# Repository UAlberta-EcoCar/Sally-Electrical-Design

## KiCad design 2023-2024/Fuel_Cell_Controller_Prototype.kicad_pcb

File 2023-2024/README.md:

# EcoCar Sally Prototype
***This is the official repository for the 2024-2025 EcoCar prototype, Sally***

Much of the systems of this vehicle will build on the innovations implemented in Lucy. Utilizing CANbus, we can easily add more modules to our overall system. We will also be employing power distribution networks alongside CANbus as to create a more intensively modular system.

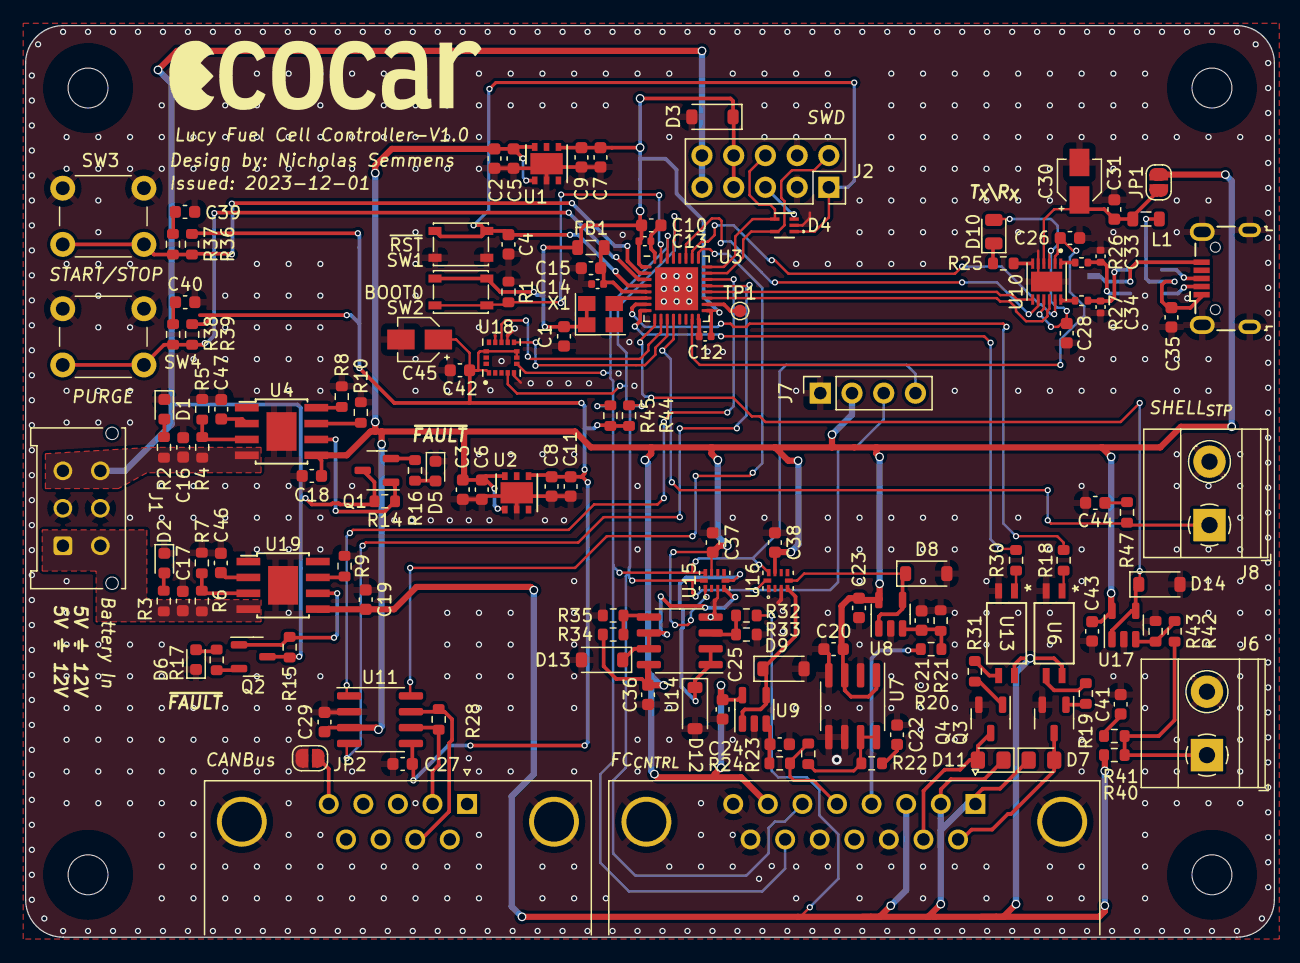
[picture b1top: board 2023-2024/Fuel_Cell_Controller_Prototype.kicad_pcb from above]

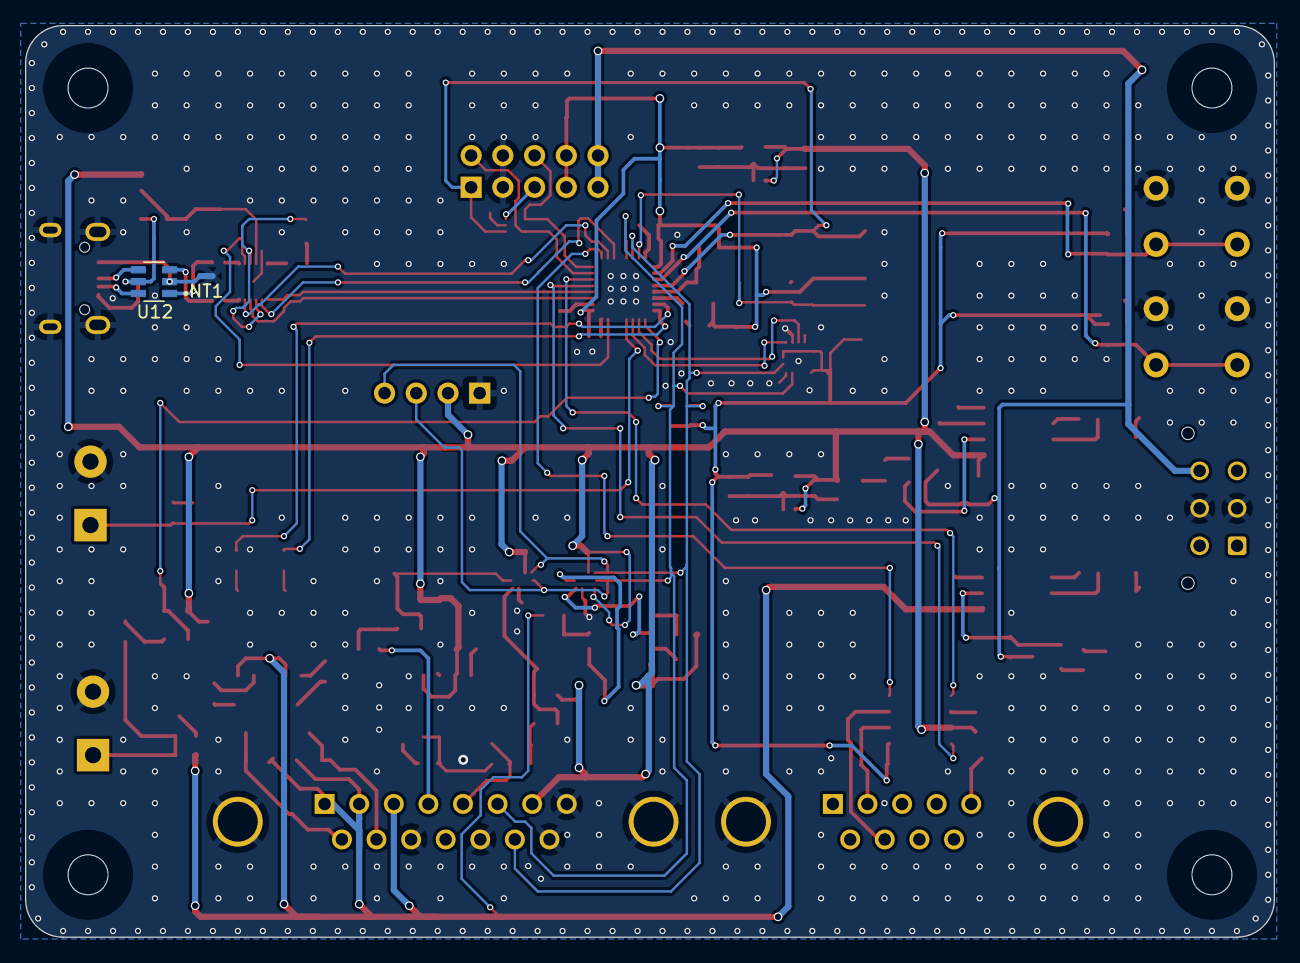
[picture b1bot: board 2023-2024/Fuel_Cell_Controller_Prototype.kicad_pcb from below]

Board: 2 copper layers, 100.0 x 73.0 mm, 148 parts (2 on the bottom side), 89 nets.

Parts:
C1, C4, C5, C6, C9, C11, C23, C25, C26, C27, C28, C29, C31, C35, C36, C37, C38, C42, C43: 100n; C_0603_1608Metric
C2, C3, C7, C8, C15, C16, C17, C18, C19, C24: 1u; C_0603_1608Metric
C10: 4u7; C_0603_1608Metric
C12, C13, C14: 100n; C_0402_1005Metric
C20, C22, C39, C40, C41, C44: 2u2; C_0603_1608Metric
C21: 0u33; C_0603_1608Metric
C30: 4u7; CP_Elec_3x5.3
C33, C34: 47p; C_0402_1005Metric
C45: 10u; CP_Elec_3x5.3
C46, C47: 2n2; C_0603_1608Metric
D1, D2: BLUE; LED_0603_1608Metric
D3, D8, D9, D12, D13, D14: MMSZ5226B-7-F; D_SOD_123_M
D4: ESDALC6V1P5
D5, D6: EMERALD; LED_0603_1608Metric
D7, D11: SD0805S020S1R0; D_0805_2012Metric_Pad1.15x1.40mm_HandSolder
D10: PINK; LED_0805_2012Metric
Display 128x64 0.96" I2C: Display_128x64; Display_128x64_096_I2C
FB1: 600R; L_0805_2012Metric
H1, H2, H3, H4: MountingHole; MountingHole_3.2mm_M3
J1: STD_PWR_HEADER
J2: Conn_02x05_Odd_Even; PinSocket_2x05_P2.54mm_Vertical
J3: DE9_Receptacle; DSUB-9_Female_Horizontal_P2.77x2.84mm_EdgePinOffset7.70mm_H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
J4: DA15_Receptacle_MountingHoles; DSUB-15_Female_Horizontal_P2.77x2.84mm_EdgePinOffset7.70mm_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
J5: USB_B_Micro; USB_Micro-B_Wuerth_629105150521
J6, J8: Screw_Terminal_01x02; TerminalBlock_Phoenix_MKDS-1,5-2-5.08_1x02_P5.08mm_Horizont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
J7: OLED; PinSocket_1x04_P2.54mm_Vertical
JP1, JP2: SolderJumper_2_Open; SolderJumper-2_P1.3mm_Open_RoundedPad1.0x1.5mm
L1: 600R/0.5A; L_0805_2012Metric
NT1: NetTie_2; NetTie-2_SMD_Pad0.5mm
Q1, Q2: SI2302A-TPMSCT-ND; SOT-23-3
Q3, Q4: FMMT491ATA; SOT-23-3
R1, R5, R7, R24, R36, R37, R38, R39, R40, R41, R47: 10k; R_0603_1608Metric
R2, R16, R17: 270; R_0603_1608Metric
R3, R43: 820; R_0603_1608Metric
R4: 11k; R_0603_1608Metric
R6: 900; R_0603_1608Metric
R8: 400k; R_0603_1608Metric
R9, R10: 1k; R_0603_1608Metric
R14, R15, R23: 100k; R_0603_1608Metric
R18, R30: 422; R_0603_1608Metric
R19, R31: 249; R_0603_1608Metric
R20: 6.8k; R_0603_1608Metric
R21, R33, R34, R35: 13k; R_0603_1608Metric
R22, R25: 51; R_0603_1608Metric
R26, R27: 33; R_0402_1005Metric
R28: 120; R_0603_1608Metric
R32: 51k; R_0603_1608Metric
R42: 2.2k; R_0603_1608Metric
R44, R45: 4.7k; R_0603_1608Metric
SW1, SW2: PTS815 SJM 250 SMTR LFS; SW_SPST_PTS810
SW3, SW4: SW_PUSH_6mm_H5mm
TP1: MCO; TestPoint_Pad_D1.0mm
U1, U2: LD39050PU33R; DFN-6-1EP_3x3mm_P0.95mm_EP1.7x2.6mm
U3: STM32L432KCUx; QFN-32-1EP_5x5mm_P0.5mm_EP3.45x3.45mm
U4, U19: TPS259621; TI_SO-PowerPAD-8
U6, U13: EL3H7(B)(TA)-VG; SOIC_BTA-VG_EVS
U7: MCP1501-33E/SN; SOIC-8_3.9x4.9mm_P1.27mm
U8, U9, U17: AD8603; TSOT-23-5
U10: FT234XD-R; SON45P300X300X80-13N
U11: MCP2542FD-E/SN; SOIC-8_3.9x4.9mm_P1.27mm
U12: USBLC6-2SC6
U14: MCP602-E/SN; SOIC-8_3.9x4.9mm_P1.27mm
U15, U16: ADS1115IRUGR; IC_ADS1115IRUGR
U18: LIS3DHTR; XDCR_LIS3DHTR
X1: OXETDLJANF-8MHZ; Crystal_SMD_3225-4Pin_3.2x2.5mm

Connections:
+3V3: C8.2, C11.2, C27.1, C42.2, C45.1, R37.2, R38.2, R44.2, R45.2, U2.4 (VO), U11.5 (VIO), U18.1 (VDD_IO), U18.7 (SDO/SA0), U18.8 (CS), U18.14 (VDD)
+5V: C2.2, C3.2, C5.2, C6.2, C18.2, C20.1, C23.2, C25.2, C29.2, C36.2, C37.2, C38.2, C43.2, J4.7, J7.2, JP1.2 (B), R34.1, U1.1 (EN), U1.6 (VI), U2.1 (EN), U2.6 (VI), U4.5 (OUT), U7.1 (VDD), U7.3 (~SHDN), U8.5 (V+), U9.5 (V+), U11.3 (VDD), U14.8 (V+), U15.1 (ADDR), U15.8 (VDD), U16.8 (VDD), U17.5 (V+)
+12V: C19.2, D7.1 (K), D11.1 (K), J4.1, J4.2, J4.3, R32.1, R40.1, U6.4, U13.4, U19.5 (OUT)
/BOOT0: R1.2, SW2.1, U3.31 (PH3)
/BTN_{1}: R36.2, R37.1, SW3.2, U3.2 (PC14)
/BTN_{2}: R38.1, R39.2, SW4.2, U3.3 (PC15)
/FLT_{5}: Q1.1 (G), R14.1, U4.6 (~FAULT)
/FLT_{12}: Q2.1 (G), R15.1, U19.6 (~FAULT)
/IO /BTN_{RTN}: J6.1, R40.2, R41.1, R42.2
/IO /CAN_H: J3.7, R28.2, U11.7 (CANH)
/IO /CAN_L: J3.2, R28.1, U11.6 (CANL)
/IO /D+: J5.3 (D+), U12.4
/IO /D-: J5.2 (D-), U12.6
/IO /DM: C33.1, R26.2, U12.1
/IO /DP: C34.1, R27.2, U12.3
/IO /FC_{TEMP}: D9.1, U9.1, U9.4 (-), U16.4 (AIN0)
/IO /GND_{1}: J5.5 (GND), NT1.2, U12.2
/IO /H2_{PRS}: D8.1, U8.1, U8.4 (-), U16.5 (AIN1)
/IO /PA0: U3.6 (PA0), X1.3 (OUT)
/IO /PA1: R18.2, U3.7 (PA1)
/IO /PA2: R30.2, U3.8 (PA2)
/IO /PA3: D14.1, U3.9 (PA3), U17.1, U17.4 (-)
/IO /PA4: U3.10 (PA4), U18.11 (INT1)
/IO /PA5: U3.11 (PA5), U18.9 (INT2)
/IO /PA6: J8.1, R47.1, U3.12 (PA6)
/IO /PA8: TP1.1, U3.18 (PA8)
/IO /PA9: U3.19 (PA9), U10.10 (RXD)
/IO /PA10: U3.20 (PA10), U10.7 (TXD)
/IO /PA11: U3.21 (PA11), U11.4 (RXD)
/IO /PA12: U3.22 (PA12), U11.1 (TXD)
/IO /PA13: D4.5, J2.2, U3.23 (PA13)
/IO /PA14: D4.4, J2.6, U3.24 (PA14)
/IO /PA15: U3.25 (PA15), U11.8 (STBY)
/IO /PB1: C26.2, U3.15 (PB1), U10.2 (~RESET#)
/IO /PB3: U3.26 (PB3), U10.11 (CTS#)
/IO /PB4: U3.27 (PB4), U10.8 (RTS#)
/IO /PB6: J4.6, J7.3, R44.1, U3.29 (PB6), U15.10 (SCL), U16.10 (SCL), U18.4 (SCL/SPC)
/IO /PB7: J4.14, J7.4, R45.1, U3.30 (PB7), U15.9 (SDA), U16.9 (SDA), U18.6 (SDA/SDI/SDO)
/IO /PRESSURE_SIG: J4.4, R20.2
/IO /PURGE_RTN: D11.2 (A), J4.10, Q4.3 (C)
/IO /Purge_Valve_Switch/V_{E}: R31.1, U13.3
/IO /SHIELD: J3.5, JP2.2 (B)
/IO /SUPPLY_RTN: D7.2 (A), J4.9, Q3.3 (C)
/IO /Supply_Valve_Switch/V_{E}: R19.1, U6.3
/IO /THERM_{VREF}: J4.5, R23.2, R24.2
/IO /VCCIO: C28.1, D10.2 (A), U10.3 (3V3OUT), U10.9 (VCCIO)
/IO /V_{BUS}: C35.1, J5.1 (VBUS), L1.2, U12.5
/MCU_3V3: C1.1, C7.2, C9.2, C10.1, C12.1, C13.1, D3.1, FB1.1, J2.7, J2.8, SW2.2, U1.4 (VO), U3.1 (VDD), U3.17 (VDD), X1.1 (Tri-State), X1.4 (VDD)
/On-Board Sensors/5V_{REF}: D13.1, U14.6 (-), U14.7, U15.4 (AIN0)
/On-Board Sensors/12V_{REF}: D12.1, U14.1, U14.2 (-), U15.5 (AIN1)
/SW_{IM}: D4.3, J2.5
/~RST: C4.1, D4.1, J2.1, SW1.2, U3.4 (NRST)
GNDA: C1.2, C2.1, C3.1, C4.2, C5.1, C6.1, C7.1, C8.1, C9.1, C10.2, C11.1, C12.2, C13.2, C14.2, C15.2, C16.1, C17.1, C18.1, C19.1, C20.2, C21.2, C22.2, C23.1, C24.2, C25.1, C26.1, C27.2, C28.2, C29.1, C30.2, C31.2, C33.2, C34.2, C35.2, C36.1, C37.1, C38.1, C39.2, C40.2, C41.2, C42.1, C43.1, C44.2, C45.2, C46.1, C47.1, D1.1 (K), D2.1 (K), D3.2, D4.2, D5.1 (K), D6.1 (K), D8.2, D9.2, D12.2, D13.2, D14.2, J1.2 (GND), J1.5 (GND), J2.3, J2.4, J3.0 (PAD), J4.0 (PAD), J4.8, J4.11 (P111), J4.13, J4.15, J5.6 (Shield), J6.2, J7.1, J8.2, JP2.1 (A), NT1.1, Q3.2 (E), Q4.2 (E), R1.1, R5.1, R7.1, R8.1, R9.1, R10.1, R21.2, R33.2, R35.2, R43.2, SW1.1, SW3.1, SW4.1, U1.2 (GND), U1.7 (GND), U2.2 (GND), U2.7 (GND), U3.16 (VSS), U3.32 (VSS), U3.33 (VSS), U4.1 (GND), U4.9 (PAD), U6.2, U7.2 (GND), U7.4 (GND), U7.5 (GND), U7.6 (GND), U8.2 (V-), U9.2 (V-), U10.5 (GND), U10.13 (GND__1), U11.2 (VSS), U13.2, U14.4 (V-), U15.3 (GND), U16.1 (ADDR), U16.3 (GND), U17.2 (V-), U18.5 (GND), U18.10 (RES), U18.12 (GND__1), U19.1 (GND), U19.9 (PAD), X1.2 (GND)
unnamed: C22.1, R22.2
unnamed: C39.1, R36.1
unnamed: C40.1, R39.1
unnamed: C41.1, R41.2
unnamed: C44.1, R47.2
unnamed: D1.2 (A), R2.1
unnamed: D2.2 (A), R3.1
unnamed: D5.2 (A), R16.1
unnamed: D6.2 (A), R17.1
unnamed: D10.1 (K), R25.1
unnamed: C30.1, C31.1, JP1.1 (A), L1.1, U10.4 (VCC)
unnamed: Q1.2 (S), R16.2
unnamed: Q2.2 (S), R17.2
unnamed: Q3.1 (B), R19.2
unnamed: Q4.1 (B), R31.2
unnamed: R18.1, U6.1
unnamed: R30.1, U13.1
unnamed: C14.1, C15.1, FB1.2, U3.5 (VDDA)
unnamed: R4.1, R5.2, U4.3 (EN/UVLO)
unnamed: R10.2, U4.7 (ILM)
unnamed: R8.2, U4.8 (OVLO)
unnamed: C47.2, U4.2 (dV/dT)
unnamed: R22.1, R23.1, U7.7 (OUT), U7.8 (FB)
unnamed: C21.1, R20.1, R21.1, U8.3 (+)
unnamed: C24.1, R24.1, U9.3 (+)
unnamed: R25.2, U10.6 (CBUS0)
unnamed: R26.1, U10.1 (USBDM)
unnamed: R27.1, U10.12 (USBDP)
unnamed: R32.2, R33.1, U14.3 (+)
unnamed: R34.2, R35.1, U14.5 (+)
unnamed: R42.1, R43.1, U17.3 (+)
unnamed: R6.1, R7.2, U19.3 (EN/UVLO)
unnamed: R9.2, U19.7 (ILM)
unnamed: C46.2, U19.2 (dV/dT)
UNPROTECTED_5V: C16.2, J1.3 (5V), J1.6 (5V), J2.9, J2.10, Q1.3 (D), Q2.3 (D), R2.2, R4.2, R14.2, R15.2, U4.4 (IN)
UNPROTECTED_12V: C17.2, J1.1 (12V), J1.4 (12V), R3.2, R6.2, U19.4 (IN)

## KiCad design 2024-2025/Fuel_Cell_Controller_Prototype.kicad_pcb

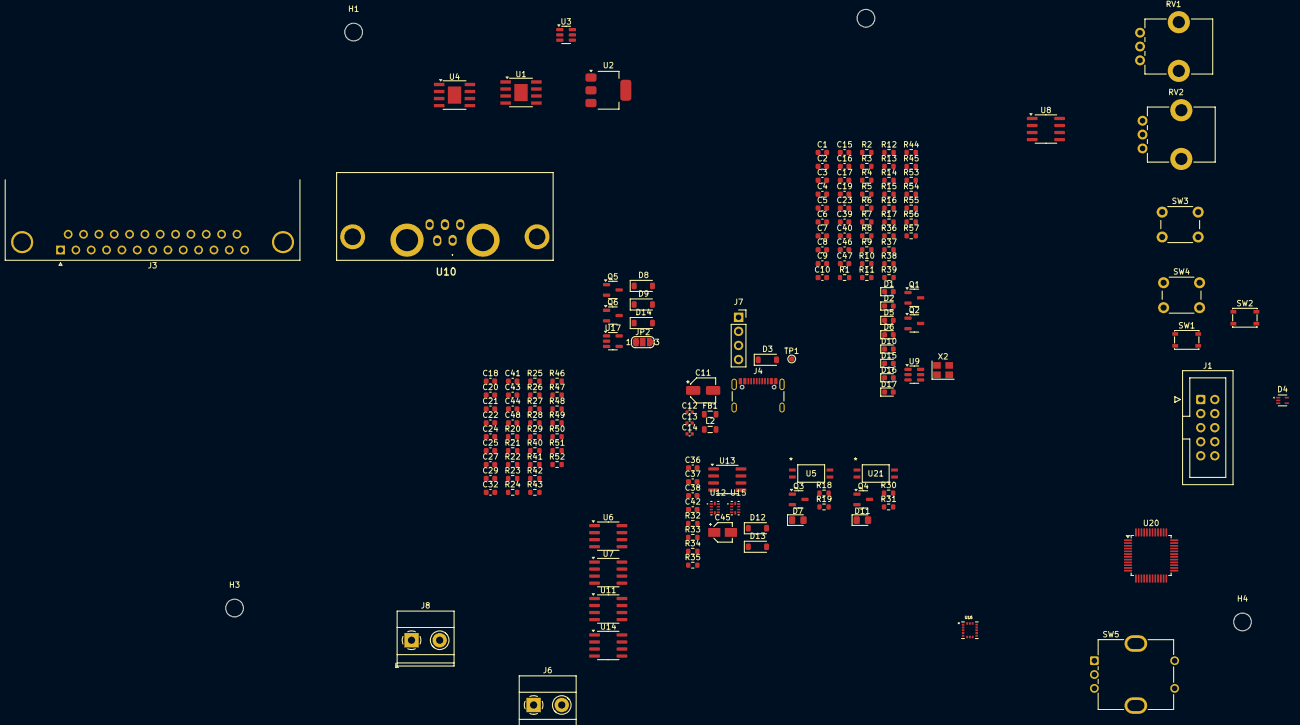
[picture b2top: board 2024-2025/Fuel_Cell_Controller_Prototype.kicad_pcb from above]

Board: 2 copper layers, 163 parts (0 on the bottom side), 108 nets, no tracks yet.

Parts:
C1, C4, C5, C8, C23, C25, C27, C29, C36, C37, C38, C42, C43, C48: 100n; C_0603_1608Metric
C2, C3, C6: 10u; C_0603_1608Metric
C7: 22u; C_0603_1608Metric
C9: 47u; C_0603_1608Metric
C10: 4u7; C_0603_1608Metric
C11: 47u; CP_Elec_4x5.4
C12, C13, C14: 100n; C_0402_1005Metric
C15, C16, C17, C19, C24: 1u; C_0603_1608Metric
C18, C32: 10n; C_0603_1608Metric
C20, C22, C39, C40, C41, C44: 2u2; C_0603_1608Metric
C21: 0u33; C_0603_1608Metric
C45: 10u; CP_Elec_3x5.3
C46, C47: 2n2; C_0603_1608Metric
D1, D2: BLUE; LED_0603_1608Metric
D3, D8, D9, D12, D13, D14: MMSZ5226B-7-F; D_SOD_123_M
D4: ESDALC6V1P5
D5, D6: EMERALD; LED_0603_1608Metric
D7, D11: SD0805S020S1R0; D_0805_2012Metric_Pad1.15x1.40mm_HandSolder
D10, D15, D16, D17: RED; LED_0603_1608Metric
Display 128x64 0.96" I2C: Display_128x64; Display_128x64_096_I2C
FB1: 600R; L_0805_2012Metric
H1, H2, H3, H4: MountingHole; MountingHole_3.2mm_M3
J1: STM32-Prog-Header; IDC-STM32-Prog-Header_2x05_P2.54mm_Vertical
J3: DB25_Receptacle_MountingHoles; DSUB-25_Female_Horizontal_P2.77x2.84mm_EdgePinOffset9.90mm_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
J4: USB_C_Receptacle_USB2.0_14P; USB_C_Receptacle_GCT_USB4105-xx-A_16P_TopMnt_Horizontal
J6, J8: Screw_Terminal_01x02; TerminalBlock_Phoenix_MKDS-1,5-2-5.08_1x02_P5.08mm_Horizont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
J7: OLED; PinSocket_1x04_P2.54mm_Vertical
JP2: SolderJumper_3_Open; SolderJumper-3_P1.3mm_Open_RoundedPad1.0x1.5mm_NumberLabels
L2: 3.3u; L_0805_2012Metric
Q1, Q2, Q5, Q6: SI2302A-TPMSCT-ND; SOT-23-3
Q3, Q4: FMMT491ATA; SOT-23-3
R1, R7, R11, R12, R24, R25, R26, R27, R29, R36, R37, R38, R39, R40, R41, R46, R47, R48, R49, R50, R51, R52: 10k; R_0603_1608Metric
R2, R16, R17: 270; R_0603_1608Metric
R3, R43: 820; R_0603_1608Metric
R4: 8k; R_0603_1608Metric
R5, R6, R9, R10, R57: 1k; R_0603_1608Metric
R8: 1.2k; R_0603_1608Metric
R13: 54.9k; R_0603_1608Metric
R14, R15, R23: 100k; R_0603_1608Metric
R18, R30: 422; R_0603_1608Metric
R19, R31: 249; R_0603_1608Metric
R20: 6.8k; R_0603_1608Metric
R21, R33, R34, R35: 13k; R_0603_1608Metric
R22: 51; R_0603_1608Metric
R28: 120; R_0603_1608Metric
R32: 51k; R_0603_1608Metric
R42: 2.2k; R_0603_1608Metric
R44, R45: 4.7k; R_0603_1608Metric
R53, R54, R55, R56: 220; R_0603_1608Metric
RV1: Purge_Delay; Potentiometer_Bourns_PTV09A-1_Single_Vertical
RV2: Purge_Duration; Potentiometer_Bourns_PTV09A-1_Single_Vertical
SW1, SW2: PTS815 SJM 250 SMTR LFS; SW_SPST_PTS810
SW3, SW4: SW_PUSH_6mm_H5mm
SW5: RotaryEncoder_Switch; RotaryEncoder_Bourns_Vertical_PEC12R-3x17F-Sxxxx
TP1: MCO; TestPoint_Pad_D1.0mm
U1, U4: TPS259631; TI_SO-PowerPAD-8
U2: AZ1117IH-3.3; SOT-223-3_TabPin2
U3: TPS565208; SOT-23-6
U5, U21: EL3H7(B)(TA)-VG; SOIC_BTA-VG_EVS
U6, U8, U13, U14: MCP6007; SOIC-8_3.9x4.9mm_P1.27mm
U7: MCP1501-33E/SN; SOIC-8_3.9x4.9mm_P1.27mm
U9: USBLC6-2SC6; SOT-23-6
U10: CANConnector; DB7W2-Male
U11: MCP2542FD-E/SN; SOIC-8_3.9x4.9mm_P1.27mm
U12, U15: ADS1115IRUGR; IC_ADS1115IRUGR
U16: LIS3DHTR; XDCR_LIS3DHTR
U17: AD8603; TSOT-23-5
U20: STM32G491CETx; LQFP-48_7x7mm_P0.5mm
X2: OXETDLJANF-8MHZ; Crystal_SMD_3225-4Pin_3.2x2.5mm

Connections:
+3.3V: C1.1, RV1.3, RV2.3, X2.1 (Tri-State), X2.4 (VDD)
+3V3: C7.2, C10.1, C12.1, C13.1, C14.1, C15.1, C27.1, C42.2, C45.1, D3.1, FB1.1, FB1.2, JP2.3 (B), R25.2, R26.2, R29.1, R37.2, R38.2, R44.2, R45.2, R46.1, R50.2, R51.2, SW2.2, U2.2 (VO), U11.5 (VIO), U16.1 (VDD_IO), U16.7 (SDO/SA0), U16.8 (CS), U16.14 (VDD), U20.1 (VBAT), U20.20 (VREF+), U20.21 (VDDA), U20.24 (VDD), U20.36 (VDD), U20.48 (VDD)
+5V: C9.1, C11.1, C20.1, C23.1, C25.1, C29.2, C36.2, C37.2, C38.2, C48.1, J3.12, J7.2, L2.2, R13.1, R34.1, U6.8 (V+), U7.1 (VDD), U7.3 (~SHDN), U8.8 (V+), U11.3 (VDD), U12.1 (ADDR), U12.8 (VDD), U13.8 (V+), U14.8 (V+), U15.8 (VDD)
+7V: C6.2, U1.5 (OUT), U2.3 (VI)
+12V: C2.1, C3.1, C5.1, C19.2, D7.1 (K), D11.1 (K), J3.1, J3.2, J3.3, J3.10, J3.11, J3.23, J3.24, JP2.1 (A), R11.2, R32.1, R40.1, U3.3 (VIN), U4.5 (OUT), U5.4, U21.4
/BTN_{1}: R36.2, R37.1, SW3.2, U20.3 (PC14)
/BTN_{2}: R38.1, R39.2, SW4.2, U20.4 (PC15)
/FLT_{7}: Q1.1 (G), R14.1, U1.6 (~FAULT)
/FLT_{12}: Q2.1 (G), R15.1, U4.6 (~FAULT)
/IO /BTN_{RTN}: J6.1, R40.2, R41.1, R42.2
/IO /CAN_H: R28.2, U10.1, U11.7 (CANH)
/IO /CAN_L: R28.1, U10.3, U11.6 (CANL)
/IO /FC_{TEMP}: D9.1, U14.6 (-), U14.7, U15.4 (AIN0)
/IO /H2_{PRS}: D8.1, U14.1, U14.2 (-), U15.5 (AIN1)
/IO /PA0: J8.1, R47.1, U20.8 (PA0)
/IO /PA1: D14.1, U17.1, U17.4 (-), U20.9 (PA1)
/IO /PA2: R52.1, U20.10 (PA2)
/IO /PA3: R27.1, U20.11 (PA3)
/IO /PA4: SW5.S1, U20.12 (PA4)
/IO /PA5: U16.11 (INT1), U20.13 (PA5)
/IO /PA6: U16.9 (INT2), U20.14 (PA6)
/IO /PA7: J3.8, R51.1, U20.15 (PA7)
/IO /PA8: TP1.1, U20.30 (PA8)
/IO /PA9: J3.21, R50.1, U20.31 (PA9)
/IO /PA10: J3.9, R25.1, U20.32 (PA10)
/IO /PA11: U9.6 (I/O1), U20.33 (PA11)
/IO /PA12: U9.4 (I/O2), U20.34 (PA12)
/IO /PA13: D4.5, J1.4 (SWDIO), U20.37 (PA13)
/IO /PA14: D4.4, J1.2 (SWCLK), U20.38 (PA14)
/IO /PB0: R30.2, U20.16 (PB0)
/IO /PB1: R18.2, U20.17 (PB1)
/IO /PB2: R54.2, U20.18 (PB2)
/IO /PB3: U6.3 (+), U20.40 (PB3)
/IO /PB4: U6.5 (+), U20.41 (PB4)
/IO /PB5: U11.4 (RXD), U20.42 (PB5)
/IO /PB6: R53.2, U20.43 (PB6)
/IO /PB7: J3.19, J7.4, R45.1, U12.9 (SDA), U15.9 (SDA), U16.6 (SDA/SDI/SDO), U20.44 (PB7)
/IO /PB8: J3.6, J7.3, R1.2, R44.1, SW2.1, U12.10 (SCL), U15.10 (SCL), U16.4 (SCL/SPC), U20.39 (PA15), U20.45 (PB8)
/IO /PB9: R55.2, U20.46 (PB9)
/IO /PB10: R56.2, U20.22 (PB10)
/IO /PB11: U11.8 (STBY), U20.25 (PB11)
/IO /PB12: J3.22, R26.1, U20.26 (PB12)
/IO /PB13: U11.1 (TXD), U20.27 (PB13)
/IO /PB14: U8.6 (-), U8.7, U20.28 (PB14)
/IO /PB15: U8.1, U8.2 (-), U20.29 (PB15)
/IO /PRESSURE_SIG: J3.4, R20.2
/IO /PURGE_RTN: D11.2 (A), J3.15, Q4.3 (C)
/IO /PWM_{1,Buff}: J3.7, Q6.3 (D), R49.1
/IO /PWM_{2,Buff}: J3.20, Q5.3 (D), R48.1
/IO /Purge_Valve_Switch/V_{E}: R31.1, U21.3
/IO /SUPPLY_RTN: D7.2 (A), J3.14, Q3.3 (C)
/IO /Supply_Valve_Switch/V_{E}: R19.1, U5.3
/IO /THERM_{VREF}: J3.5, R23.2, R24.2
/On-Board Sensors/5V_{REF}: D13.1, U12.4 (AIN0), U13.6 (-), U13.7
/On-Board Sensors/12V_{REF}: D12.1, U12.5 (AIN1), U13.1, U13.2 (-)
/PF0: U20.5 (PF0), X2.3 (OUT)
/P_Delay: RV1.2, U8.3 (+)
/P_Dur: RV2.2, U8.5 (+)
/VBUS: J4.A4 (VBUS), J4.A9 (VBUS), J4.B4 (VBUS), J4.B9 (VBUS), U9.5 (VBUS)
/~RST: C4.1, SW1.2, U20.7 (PG10)
GNDA: C1.2, C2.2, C3.2, C4.2, C5.2, C6.1, C7.1, C9.2, C10.2, C11.2, C12.2, C13.2, C14.2, C15.2, C16.1, C17.1, C18.2, C19.1, C20.2, C21.2, C22.2, C23.2, C24.2, C25.2, C27.2, C29.1, C32.2, C36.1, C37.1, C38.1, C39.2, C40.2, C41.2, C42.1, C43.1, C44.2, C45.2, C46.1, C47.1, C48.2, D1.1 (K), D2.1 (K), D3.2, D4.2, D8.2, D9.2, D10.1 (K), D12.2, D13.2, D14.2, D15.1 (K), D16.1 (K), D17.1 (K), J1.5 (GND), J1.6 (GND), J3.0 (PAD), J3.13, J3.16, J3.18, J3.25, J4.A1 (GND), J4.A12 (GND), J4.B1 (GND), J4.B12 (GND), J4.S1 (SHIELD), J6.2, J7.1, J8.2, Q1.2 (S), Q2.2 (S), Q3.2 (E), Q4.2 (E), Q5.2 (S), Q6.2 (S), R1.1, R8.1, R9.1, R10.1, R12.1, R21.2, R33.2, R35.2, R43.2, R57.1, RV1.1, RV2.1, SW1.1, SW3.1, SW4.1, SW5.C, SW5.S2, U1.1 (GND), U1.9 (PAD), U2.1 (GND), U3.1 (GND), U4.1 (GND), U4.9 (PAD), U5.2, U6.4 (V-), U7.2 (GND), U7.4 (GND), U7.5 (GND), U7.6 (GND), U8.4 (V-), U9.2 (GND), U10.8 (A1), U11.2 (VSS), U12.3 (GND), U13.4 (V-), U14.4 (V-), U15.1 (ADDR), U15.3 (GND), U16.5 (GND), U16.10 (RES), U16.12 (GND__1), U17.2 (V-), U20.19 (VSSA), U20.23 (VSS), U20.35 (VSS), U20.47 (VSS), U21.2, X2.2 (GND)
unnamed: C18.1, R29.2, R52.2, SW5.A
unnamed: C22.1, R22.2
unnamed: C32.1, R27.2, R46.2, SW5.B
unnamed: C39.1, R36.1
unnamed: C40.1, R39.1
unnamed: C41.1, R41.2
unnamed: C44.1, R47.2
unnamed: D1.2 (A), R2.1
unnamed: D2.2 (A), R3.1
unnamed: D5.2 (A), R16.1
unnamed: D5.1 (K), Q1.3 (D)
unnamed: D6.2 (A), R17.1
unnamed: D6.1 (K), Q2.3 (D)
unnamed: D10.2 (A), R53.1
unnamed: D15.2 (A), R54.1
unnamed: D16.2 (A), R55.1
unnamed: D17.2 (A), R56.1
unnamed: J4.A6 (D+), J4.B6 (D+), U9.3 (I/O2)
unnamed: J4.A7 (D-), J4.B7 (D-), U9.1 (I/O1)
unnamed: JP2.2 (C), R48.2, R49.2
unnamed: Q3.1 (B), R19.2
unnamed: Q4.1 (B), R31.2
unnamed: Q5.1 (G), U6.6 (-), U6.7
unnamed: Q6.1 (G), U6.1, U6.2 (-)
unnamed: R18.1, U5.1
unnamed: R30.1, U21.1
unnamed: R4.1, R5.2, U1.3 (EN/UVLO)
unnamed: R10.2, U1.7 (ILM)
unnamed: R5.1, R8.2, U1.8 (OVLO)
unnamed: C47.2, U1.2 (dV/dT)
unnamed: R11.1, U3.5 (EN)
unnamed: C8.1, L2.1, U3.2 (SW)
unnamed: C8.2, U3.6 (VBST)
unnamed: R12.2, R13.2, U3.4 (VFB)
unnamed: R6.2, R7.1, U4.3 (EN/UVLO)
unnamed: R9.2, U4.7 (ILM)
unnamed: R6.1, R57.2, U4.8 (OVLO)
unnamed: C46.2, U4.2 (dV/dT)
unnamed: R22.1, R23.1, U7.7 (OUT), U7.8 (FB)
unnamed: R32.2, R33.1, U13.3 (+)
unnamed: R34.2, R35.1, U13.5 (+)
unnamed: C21.1, R20.1, R21.1, U14.3 (+)
unnamed: C24.1, R24.1, U14.5 (+)
unnamed: R42.1, R43.1, U17.3 (+)
unnamed: C43.2, U17.5 (V+)
UNPROTECTED_7V: C16.2, R2.2, R4.2, R14.2, R15.2, R16.2, R17.2, U1.4 (IN)
UNPROTECTED_12V: C17.2, R3.2, R7.2, U4.4 (IN), U10.2, U10.4, U10.5

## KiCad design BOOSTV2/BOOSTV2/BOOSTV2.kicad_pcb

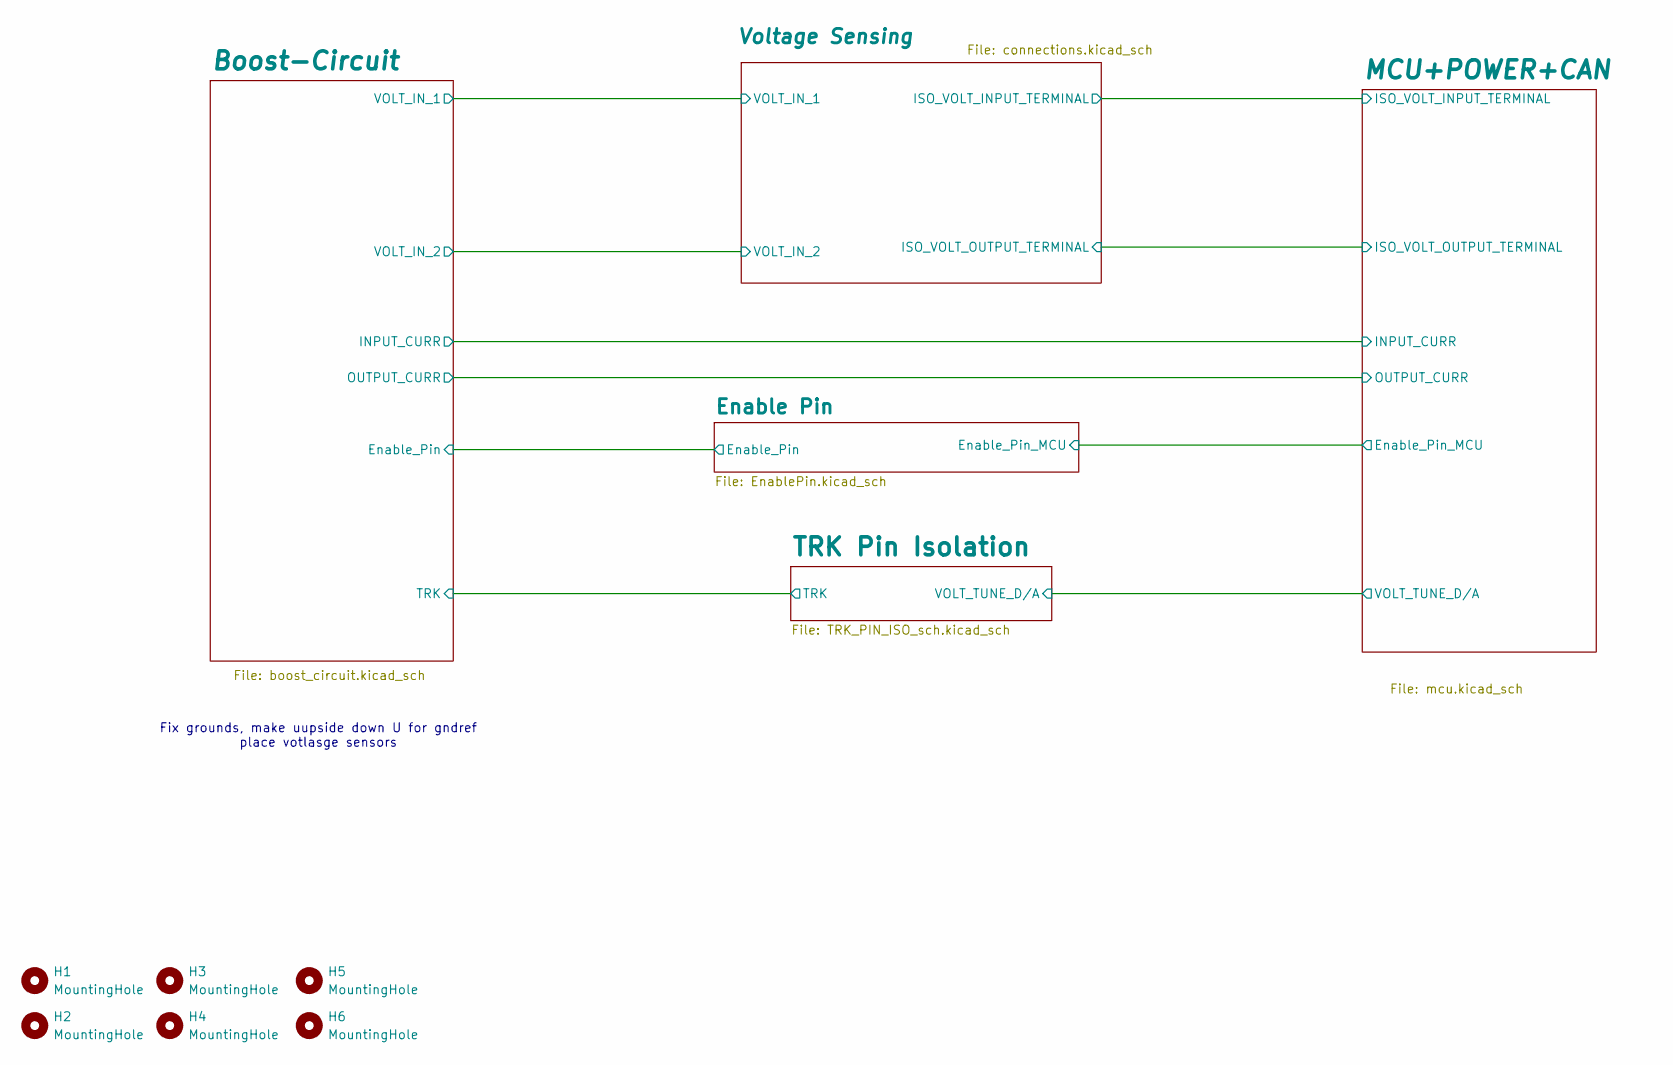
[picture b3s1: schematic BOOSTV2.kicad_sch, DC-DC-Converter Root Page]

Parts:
H1, H2, H3, H4, H5, H6: MountingHole; MountingHole_3.5mm

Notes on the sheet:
Fix grounds, make uupside down U for gndref place votlasge sensors

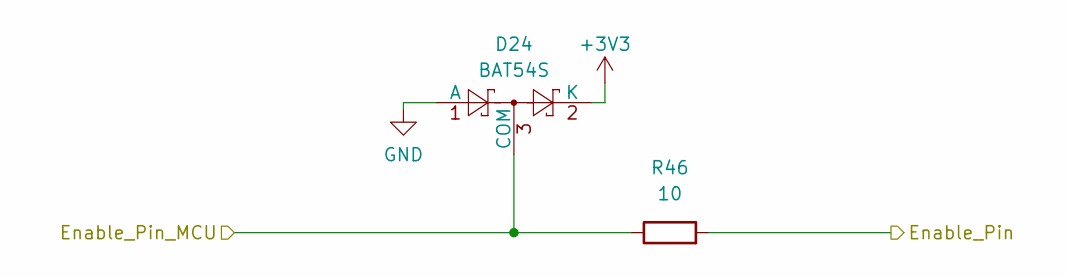
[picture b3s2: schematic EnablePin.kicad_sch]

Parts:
D24: BAT54S; SOT-23
R46: 10; R_0603_1608Metric

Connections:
+3V3: D24.2 (K); also elsewhere on the board
/Boost-Circuit/Enable_Pin: R46.2; also elsewhere on the board
/Enable Pin/Enable_Pin_MCU: D24.3 (COM), R46.1; also elsewhere on the board
GND: D24.1 (A); also elsewhere on the board

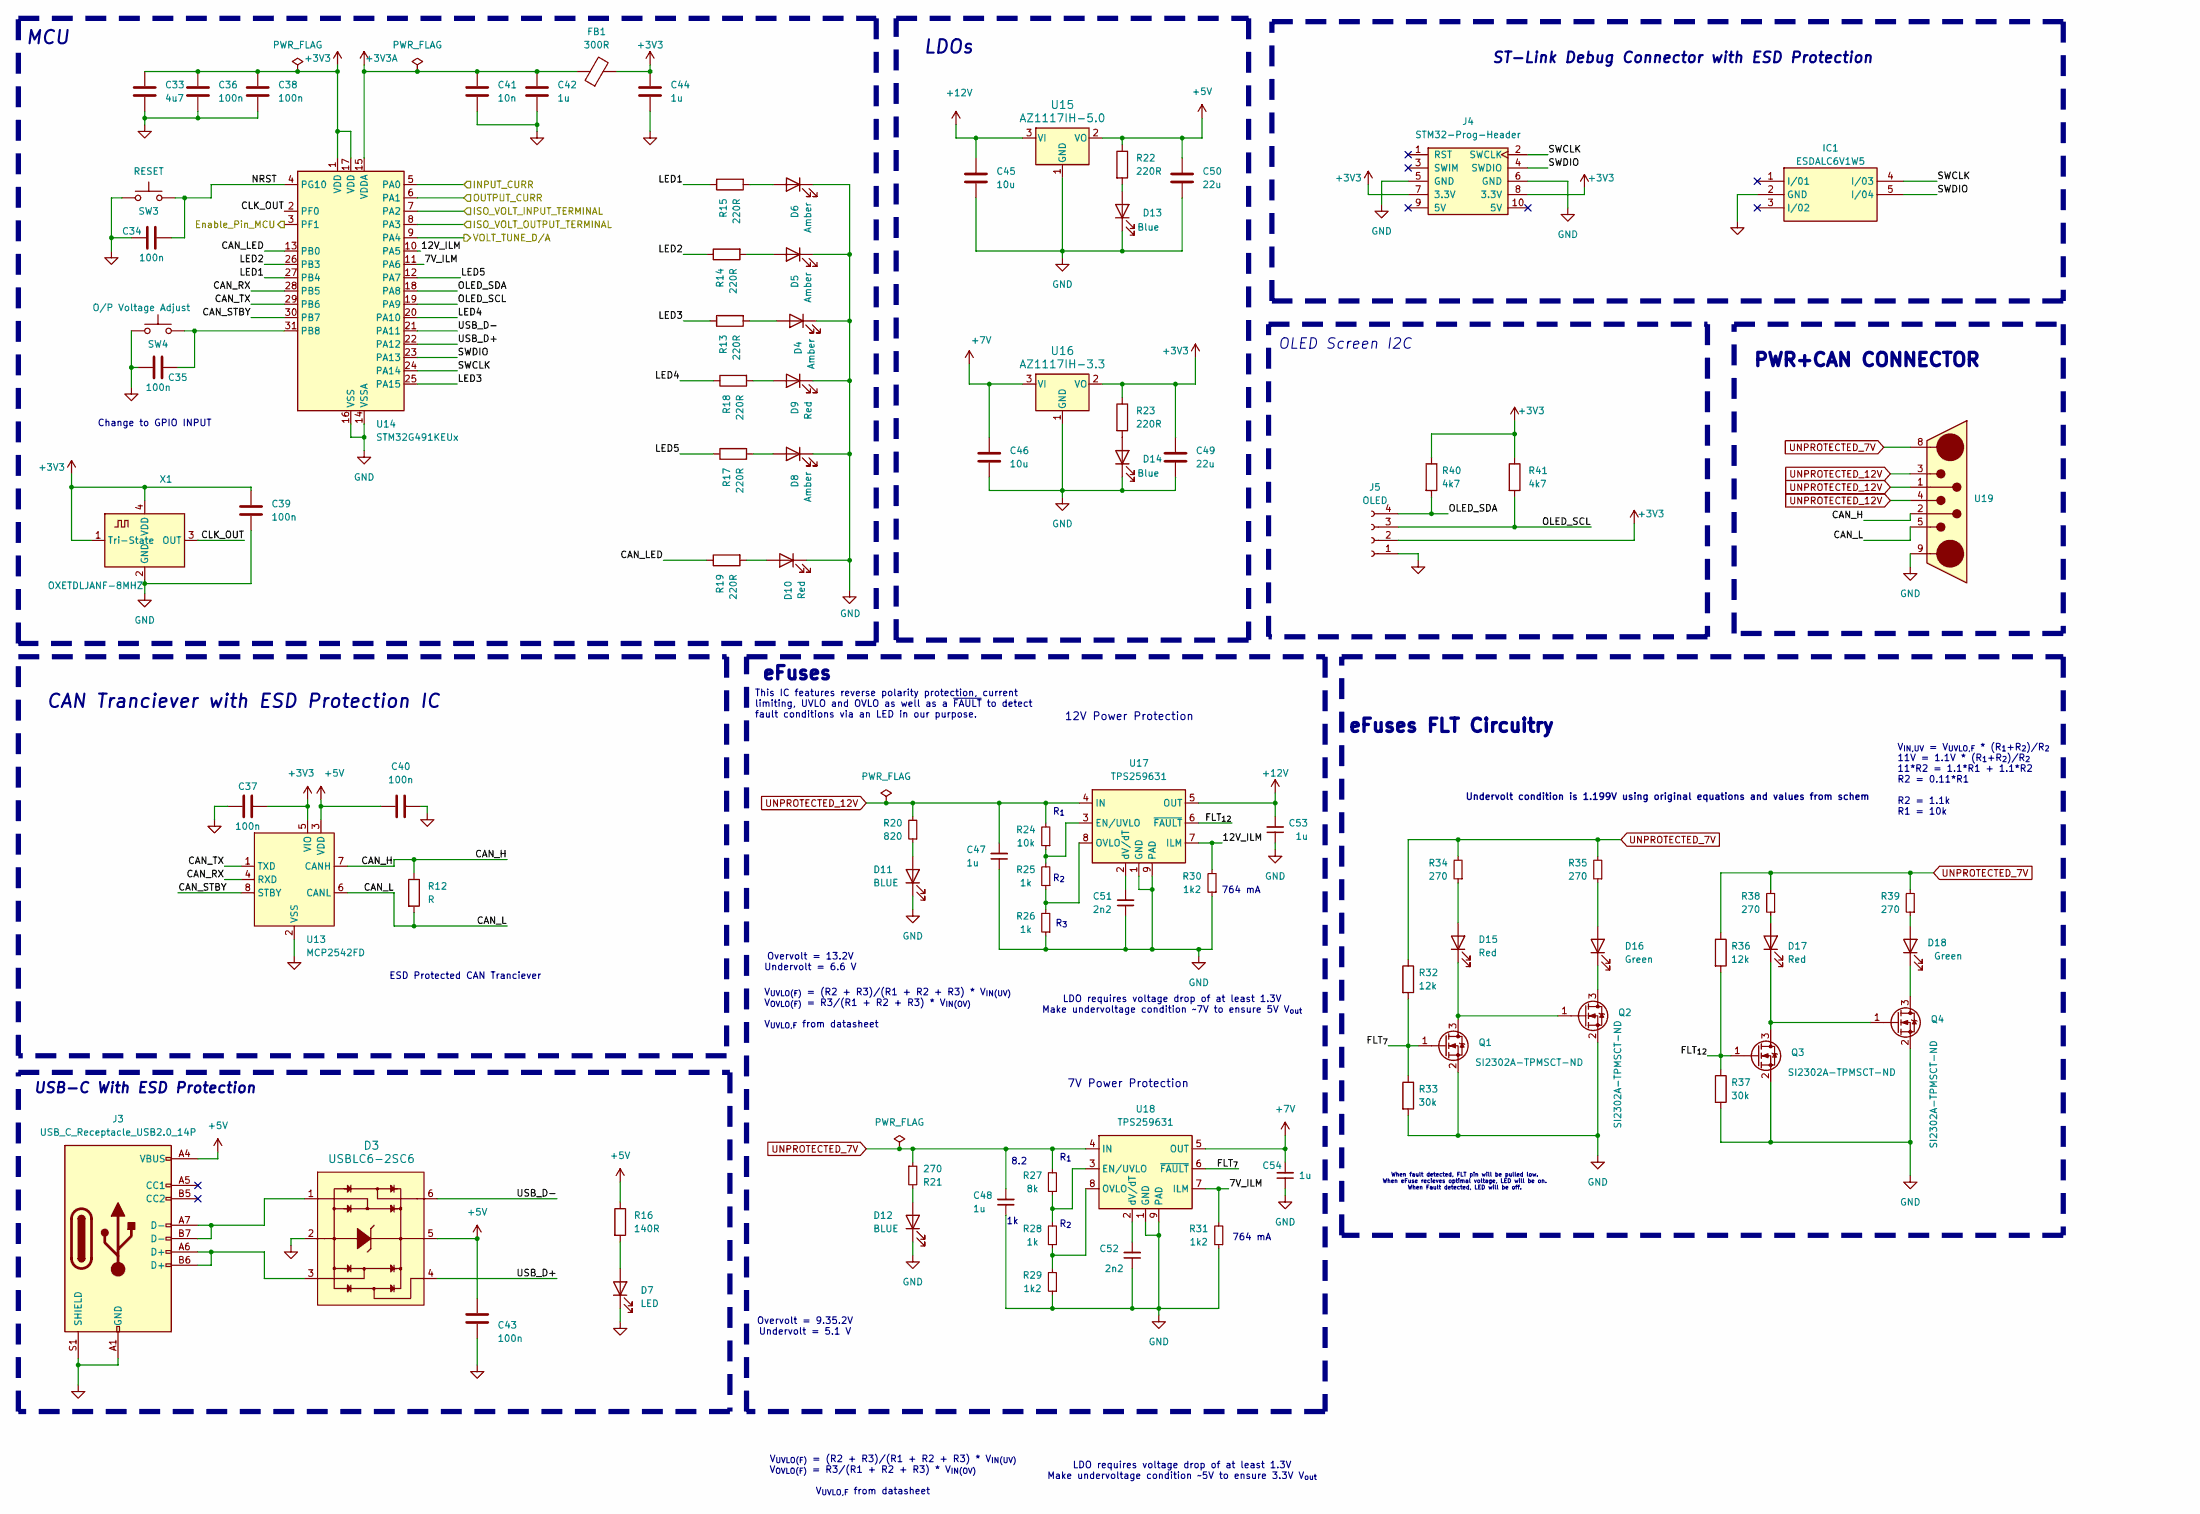
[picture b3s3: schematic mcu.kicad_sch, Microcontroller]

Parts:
C33: 4u7; C_0603_1608Metric; JLCPCB Part#(Optional) C96446
C34, C35, C36, C37, C38, C40, C43: 100n; C_0603_1608Metric; JLCPCB Part#(Optional) C1525
C39: 100n; C_0603_1608Metric
C41: 10n; C_0603_1608Metric; JLCPCB Part#(Optional) C96446
C42, C44: 1u; C_0603_1608Metric; JLCPCB Part#(Optional) C28323
C45, C46: 10u; C_0603_1608Metric
C47, C48, C53, C54: 1u; C_0603_1608Metric; Part# C15849
C49, C50: 22u; C_0603_1608Metric
C51, C52: 2n2; C_0603_1608Metric; Part# C1604
D3: USBLC6-2SC6; SOT95P280X145-6N; Digikey # 497-5235-1-ND
D4, D5, D6, D8: Amber; LED_0603_1608Metric
D7: LED; LED_0603_1608Metric
D9, D10: Red; LED_0603_1608Metric
D11, D12: BLUE; LED_0603_1608Metric; Part# C72041
D13, D14: Blue; LED_0603_1608Metric
D15, D17: Red; LED_0603_1608Metric; Part# C72043
D16, D18: Green; LED_0603_1608Metric; Part# C72043
FB1: 300R; L_0603_1608Metric; Digikey # 1934-1474-1-ND
IC1: ESDALC6V1W5; SOT65P210X110-5N; JLCPCB Part#(Optional) C2827626
J3: USB_C_Receptacle_USB2.0_14P; USB_C_Receptacle_GCT_USB4105-xx-A_16P_TopMnt_Horizontal
J4: STM32-Prog-Header; IDC-STM32-Prog-Header_2x05_P2.54mm_Vertical
J5: OLED; Display_128x64_096_I2C
Q1, Q2, Q3, Q4: SI2302A-TPMSCT-ND; SOT-23-3_Adjusted; Part# SI2302A-TPMSCT-ND
R12: R; R_0603_1608Metric
R13, R14, R15, R17, R18, R19, R22, R23: 220R; R_0603_1608Metric
R16: 140R; R_0603_1608Metric
R20: 820; R_0603_1608Metric; Part# C23253
R21, R34, R35, R38, R39: 270; R_0603_1608Metric; Part# C22966
R24: 10k; R_0603_1608Metric
R25, R26, R28: 1k; R_0603_1608Metric
R27: 8k; R_0603_1608Metric
R29, R30, R31: 1k2; R_0603_1608Metric
R32, R36: 12k; R_0603_1608Metric
R33, R37: 30k; R_0603_1608Metric
R40, R41: 4k7; R_0603_1608Metric
SW3: RESET; SW_PUSH_6mm_H5mm; Part # C2689510
SW4: O/P Voltage Adjust; SW_PUSH_6mm_H5mm; Part # C2689510
U13: MCP2542FD; SOIC-8_3.9x4.9mm_P1.27mm
U14: STM32G491KEUx; QFN-32-1EP_5x5mm_P0.5mm_EP3.45x3.45mm
U15: AZ1117IH-5.0; SOT-223-3_TabPin2
U16: AZ1117IH-3.3; SOT-223-3_TabPin2
U17, U18: TPS259631; TI_SO-PowerPAD-8
U19: DB7W2-Male
X1: OXETDLJANF-8MHZ; Crystal_SMD_3225-4Pin_3.2x2.5mm

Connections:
+3V3: C33.1, C36.1, C37.2, C38.1, C39.1, C44.1, C49.1, FB1.2, J4.7 (3.3V), J4.8 (3.3V), J5.2, R23.1, R40.1, R41.1, U13.5 (VIO), U14.1 (VDD), U14.17 (VDD), U16.2 (VO), X1.1 (Tri-State), X1.4 (VDD); also elsewhere on the board
+3V3A: C41.1, C42.1, FB1.1, U14.15 (VDDA)
+5V: C40.2, C43.2, C50.1, D3.5, J3.A4 (VBUS), J3.A9 (VBUS), J3.B4 (VBUS), J3.B9 (VBUS), R16.1, R22.1, U13.3 (VDD), U15.2 (VO); also elsewhere on the board
+7V: C46.1, C54.2, U16.3 (VI), U18.5 (OUT)
+12V: C45.1, C53.2, U15.3 (VI), U17.5 (OUT)
/Boost-Circuit/INPUT_CURR: U14.5 (PA0); also elsewhere on the board
/Boost-Circuit/OUTPUT_CURR: U14.6 (PA1); also elsewhere on the board
/Enable Pin/Enable_Pin_MCU: U14.3 (PF1); also elsewhere on the board
/Low Side/7V_ILM: R31.2, U14.11 (PA6), U18.7 (ILM)
/Low Side/12V_ILM: R30.2, U14.10 (PA5), U17.7 (ILM)
/Low Side/CAN_H: R12.1, U13.7 (CANH), U19.2
/Low Side/CAN_L: R12.2, U13.6 (CANL), U19.5
/Low Side/CAN_LED: R19.1, U14.13 (PB0)
/Low Side/CAN_RX: U13.4 (RXD), U14.28 (PB5)
/Low Side/CAN_STBY: U13.8 (STBY), U14.30 (PB7)
/Low Side/CAN_TX: U13.1 (TXD), U14.29 (PB6)
/Low Side/CLK_OUT: U14.2 (PF0), X1.3 (OUT)
/Low Side/FLT_{7}: Q1.1 (G), R32.2, R33.1, U18.6 (~FAULT)
/Low Side/FLT_{12}: Q3.1 (G), R36.2, R37.1, U17.6 (~FAULT)
/Low Side/ISO_VOLT_INPUT_TERMINAL: U14.7 (PA2); also elsewhere on the board
/Low Side/ISO_VOLT_OUTPUT_TERMINAL: U14.8 (PA3); also elsewhere on the board
/Low Side/LED1: R15.1, U14.27 (PB4)
/Low Side/LED2: R14.1, U14.26 (PB3)
/Low Side/LED3: R13.1, U14.25 (PA15)
/Low Side/LED4: R18.1, U14.20 (PA10)
/Low Side/LED5: R17.1, U14.12 (PA7)
/Low Side/NRST: C34.2, SW3.2, U14.4 (PG10)
/Low Side/OLED_SCL: J5.3, R41.2, U14.19 (PA9)
/Low Side/OLED_SDA: J5.4, R40.2, U14.18 (PA8)
/Low Side/SWCLK: IC1.4 (I/03), J4.2 (SWCLK), U14.24 (PA14)
/Low Side/SWDIO: IC1.5 (I/04), J4.4 (SWDIO), U14.23 (PA13)
/Low Side/USB_D+: D3.4, U14.22 (PA12)
/Low Side/USB_D-: D3.6, U14.21 (PA11)
/Low Side/VOLT_TUNE_D/A: U14.9 (PA4); also elsewhere on the board
GND: C33.2, C34.1, C35.1, C36.2, C37.1, C38.2, C39.2, C40.1, C41.2, C42.2, C43.1, C44.2, C45.2, C46.2, C47.1, C48.1, C49.2, C50.2, C51.1, C52.1, C53.1, C54.1, D3.2, D4.1 (K), D5.1 (K), D6.1 (K), D7.1 (K), D8.1 (K), D9.1 (K), D10.1 (K), D11.1 (K), D12.1 (K), D13.1 (K), D14.1 (K), IC1.2 (GND), J3.A1 (GND), J3.A12 (GND), J3.B1 (GND), J3.B12 (GND), J3.S1 (SHIELD), J4.5 (GND), J4.6 (GND), J5.1, Q1.2 (S), Q2.2 (S), Q3.2 (S), Q4.2 (S), R26.1, R29.1, R30.1, R31.1, R33.2, R37.2, SW3.1, SW4.2, U13.2 (VSS), U14.14 (VSSA), U14.16 (VSS), U14.32 (VSS), U14.33 (VSS), U15.1 (GND), U16.1 (GND), U17.1 (GND), U17.9 (PAD), U18.1 (GND), U18.9 (PAD), U19.9, X1.2 (GND); also elsewhere on the board
unnamed: D3.1, J3.A7 (D-), J3.B7 (D-)
unnamed: D3.3, J3.A6 (D+), J3.B6 (D+)
unnamed: D4.2 (A), R13.2
unnamed: D5.2 (A), R14.2
unnamed: D6.2 (A), R15.2
unnamed: D7.2 (A), R16.2
unnamed: D8.2 (A), R17.2
unnamed: D9.2 (A), R18.2
unnamed: D10.2 (A), R19.2
unnamed: D11.2 (A), R20.1
unnamed: D12.2 (A), R21.2
unnamed: D13.2 (A), R22.2
unnamed: D14.2 (A), R23.2
unnamed: D15.2 (A), R34.1
unnamed: D15.1 (K), Q1.3 (D), Q2.1 (G)
unnamed: D16.2 (A), R35.1
unnamed: D16.1 (K), Q2.3 (D)
unnamed: D17.2 (A), R38.1
unnamed: D17.1 (K), Q3.3 (D), Q4.1 (G)
unnamed: D18.2 (A), R39.1
unnamed: D18.1 (K), Q4.3 (D)
unnamed: C35.2, SW4.1, U14.31 (PB8)
unnamed: R24.1, R25.2, U17.3 (EN/UVLO)
unnamed: R25.1, R26.2, U17.8 (OVLO)
unnamed: C51.2, U17.2 (dV/dT)
unnamed: R27.1, R28.2, U18.3 (EN/UVLO)
unnamed: R28.1, R29.2, U18.8 (OVLO)
unnamed: C52.2, U18.2 (dV/dT)
UNPROTECTED_7V: C48.2, R21.1, R27.2, R32.1, R34.2, R35.2, R36.1, R38.2, R39.2, U18.4 (IN), U19.8
UNPROTECTED_12V: C47.2, R20.2, R24.2, U17.4 (IN), U19.1, U19.3, U19.4

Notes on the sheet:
764 mA
V_{UVLO(F)} = (R2 + R3)/(R1 + R2 + R3) * V_{IN(UV)} V_{OVLO(F)} = R3/(R1 + R2 + R3) * V_{IN(OV)} V_{UVLO,F} from datasheet
V_{IN,UV} = V_{UVLO,F} * (R_{1}+R_{2})/R_{2} 11V = 1.1V * (R_{1}+R_{2})/R_{2} 11*R2 = 1.1*R1 + 1.1*R2 R2 = 0.11*R1 R2 = 1.1k R1 = 10k
MCU
Undervolt condition is 1.199V using original equations and values from schem
LDO requires voltage drop of at least 1.3V Make undervoltage condition ~7V to ensure 5V V_{out}
Overvolt = 13.2V Undervolt = 6.6 V
PWR+CAN CONNECTOR
ST-Link Debug Connector with ESD Protection
8.2
USB-C With ESD Protection
R_{1}
LDOs
CAN Tranciever with ESD Protection IC
R_{2}
LDO requires voltage drop of at least 1.3V Make undervoltage condition ~5V to ensure 3.3V V_{out}
When fault detected, FLT pin will be pulled low. When eFuse recieves optimal voltage, LED will be on. When Fault detected, LED will be off.
Change to GPIO INPUT
eFuses
ESD Protected CAN Tranciever
This IC features reverse polarity protection, current limiting, UVLO and OVLO as well as a ~{FAULT} to detect fault conditions via an LED in our purpose.
V_{UVLO(F)} = (R2 + R3)/(R1 + R2 + R3) * V_{IN(UV)} V_{OVLO(F)} = R3/(R1 + R2 + R3) * V_{IN(OV)} V_{UVLO,F} from datasheet
Overvolt = 9.35.2V Undervolt = 5.1 V
7V Power Protection
OLED Screen I2C
R_{3}
12V Power Protection
eFuses FLT Circuitry
